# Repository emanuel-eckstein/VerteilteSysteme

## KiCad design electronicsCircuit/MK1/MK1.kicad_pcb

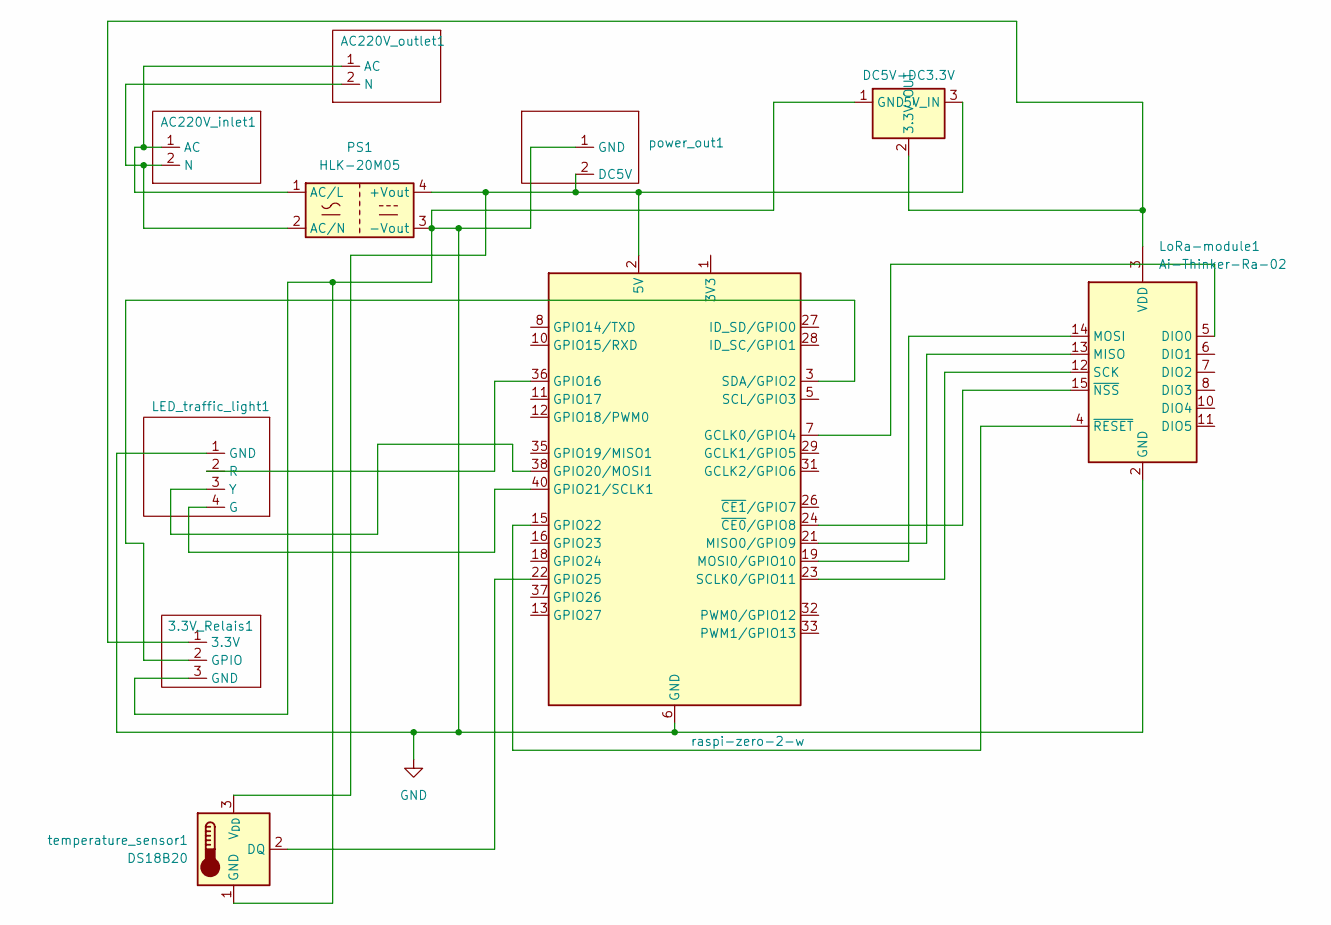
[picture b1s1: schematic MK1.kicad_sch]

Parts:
3.3V_Relais1: PinHeader_1x03_P2.54mm_Vertical
AC220V_inlet1, AC220V_outlet1: TerminalBlock_bornier-2_P5.08mm
J1: raspi-zero-2-w; Raspberry_Pi_Zero_Socketed_THT_FaceDown_MountingHoles
LED_traffic_light1: PinHeader_1x04_P2.54mm_Vertical
LoRa-module1: Ai-Thinker-Ra-02; LoRa2
PS1: HLK-20M05; Converter_ACDC_Hi-Link_HLK-20Mxx
U2: DC5V-DC3.3V; Converter_DCDC_Murata_OKI-78SR_Vertical
power_out1: PinHeader_1x02_P2.54mm_Vertical
temperature_sensor1: DS18B20; PinHeader_1x03_P2.54mm_Vertical

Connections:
GND: 3.3V_Relais1.3 (GND), J1.6 (GND), J1.9 (GND), J1.14 (GND), J1.20 (GND), J1.25 (GND), J1.30 (GND), J1.34 (GND), J1.39 (GND), LED_traffic_light1.1 (GND), LoRa-module1.1 (GND), LoRa-module1.2 (GND), LoRa-module1.9 (GND), LoRa-module1.16 (GND), PS1.3 (-Vout), U2.1 (GND), power_out1.1 (GND), temperature_sensor1.1 (GND)
unnamed: 3.3V_Relais1.1 (3.3V), LoRa-module1.3 (VDD), U2.2 (3.3V_OUT)
unnamed: 3.3V_Relais1.2 (GPIO), J1.3 (SDA/GPIO2)
unnamed: AC220V_inlet1.1 (AC), AC220V_outlet1.1 (AC), PS1.1 (AC/L)
unnamed: AC220V_inlet1.2 (N), AC220V_outlet1.2 (N), PS1.2 (AC/N)
unnamed: J1.1 (3V3), J1.17 (3V3)
unnamed: J1.7 (GCLK0/GPIO4), LoRa-module1.5 (DIO0)
unnamed: J1.36 (GPIO16), LED_traffic_light1.2 (R)
unnamed: J1.38 (GPIO20/MOSI1), LED_traffic_light1.3 (Y)
unnamed: J1.40 (GPIO21/SCLK1), LED_traffic_light1.4 (G)
unnamed: J1.15 (GPIO22), LoRa-module1.4 (~RESET)
unnamed: J1.22 (GPIO25), temperature_sensor1.2 (DQ)
unnamed: J1.21 (MISO0/GPIO9), LoRa-module1.13 (MISO)
unnamed: J1.19 (MOSI0/GPIO10), LoRa-module1.14 (MOSI)
unnamed: J1.23 (SCLK0/GPIO11), LoRa-module1.12 (SCK)
unnamed: J1.24 (~CE0/GPIO8), LoRa-module1.15 (~NSS)
unnamed: J1.2 (5V), J1.4 (5V), PS1.4 (+Vout), U2.3 (5V_IN), power_out1.2 (DC5V), temperature_sensor1.3 (V_{DD})

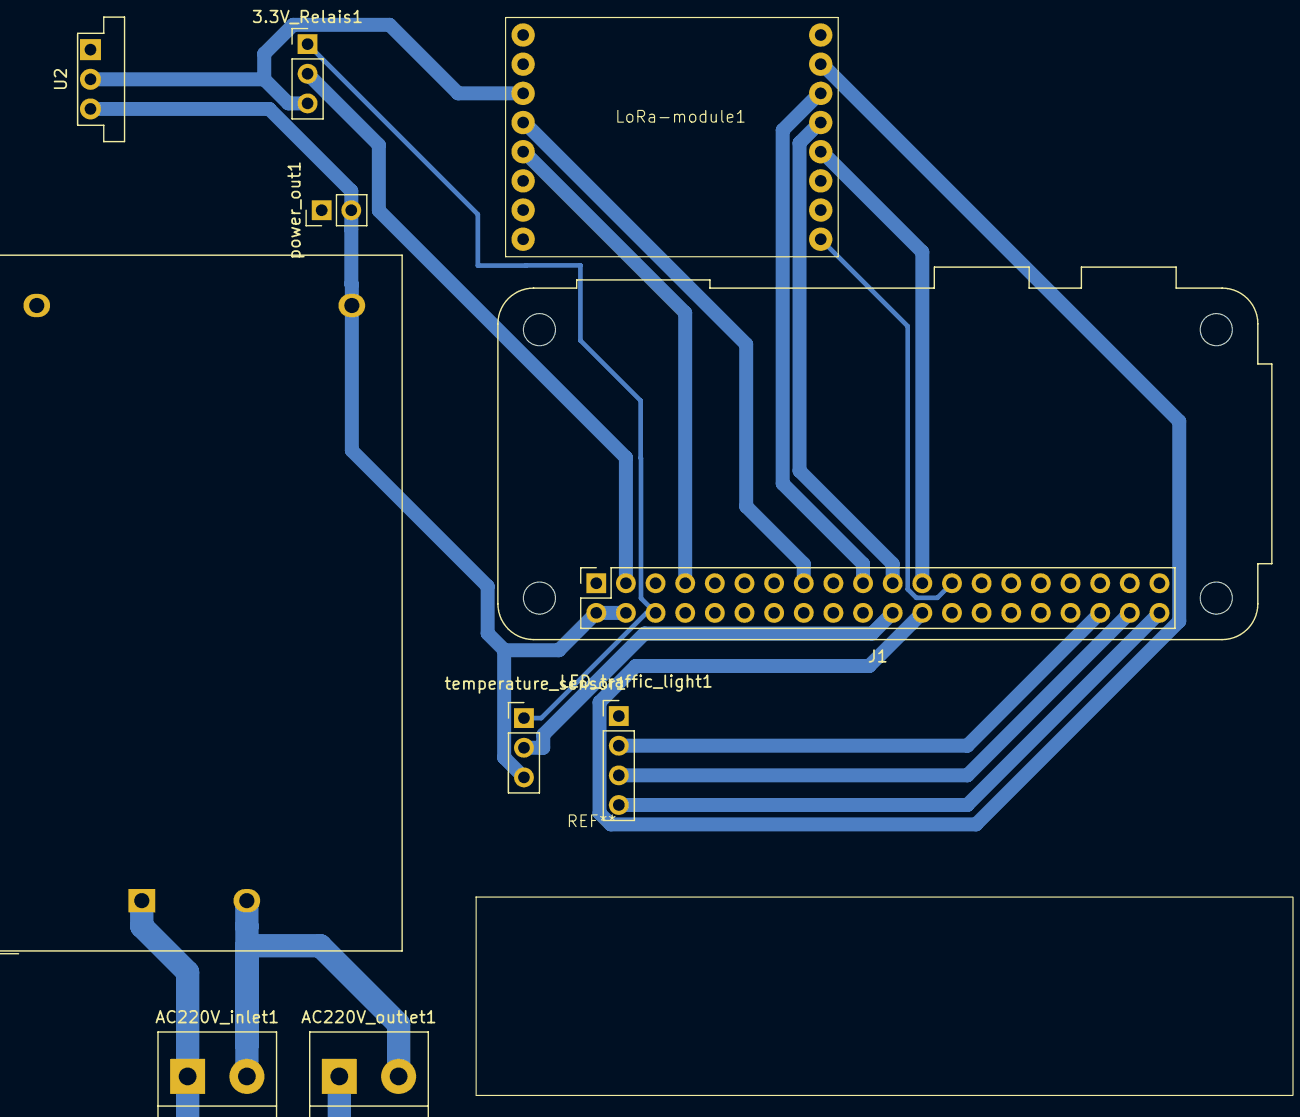
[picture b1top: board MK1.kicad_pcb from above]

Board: 2 copper layers, 10 parts (0 on the bottom side), 17 nets.

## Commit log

2024-08-23 big push
2024-09-28 different files added
2024-09-29 added client, server and others
2024-09-30 alles neu
